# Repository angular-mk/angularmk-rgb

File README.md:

# angularmk-rgb
## Angular RGB Mechanical Keyboard

### Description

The AngularRGB is a, minimalistic, 40% keyboard that supports perkey RGB Lighting. We've noticed that there are no purchasing options for anyone interested in a rgb per key backlit keyboard, so we decided to create one.
[Website Description](https://angularmk.xyz/angular-rgb/)

The PCB consists of a 4x12 matrix layed out as a COL to ROW diode configuration with a staggered design. Additionally, there are slots cut out on the board to provide the space for the WS2812B-Mini RGB LEDs that provide the lighting. There are also numerous protection features, such as ESD protections for both the data lines aswell as the power lines; fueses protecting the precious microcontroller in a case of short circuit; and many more.

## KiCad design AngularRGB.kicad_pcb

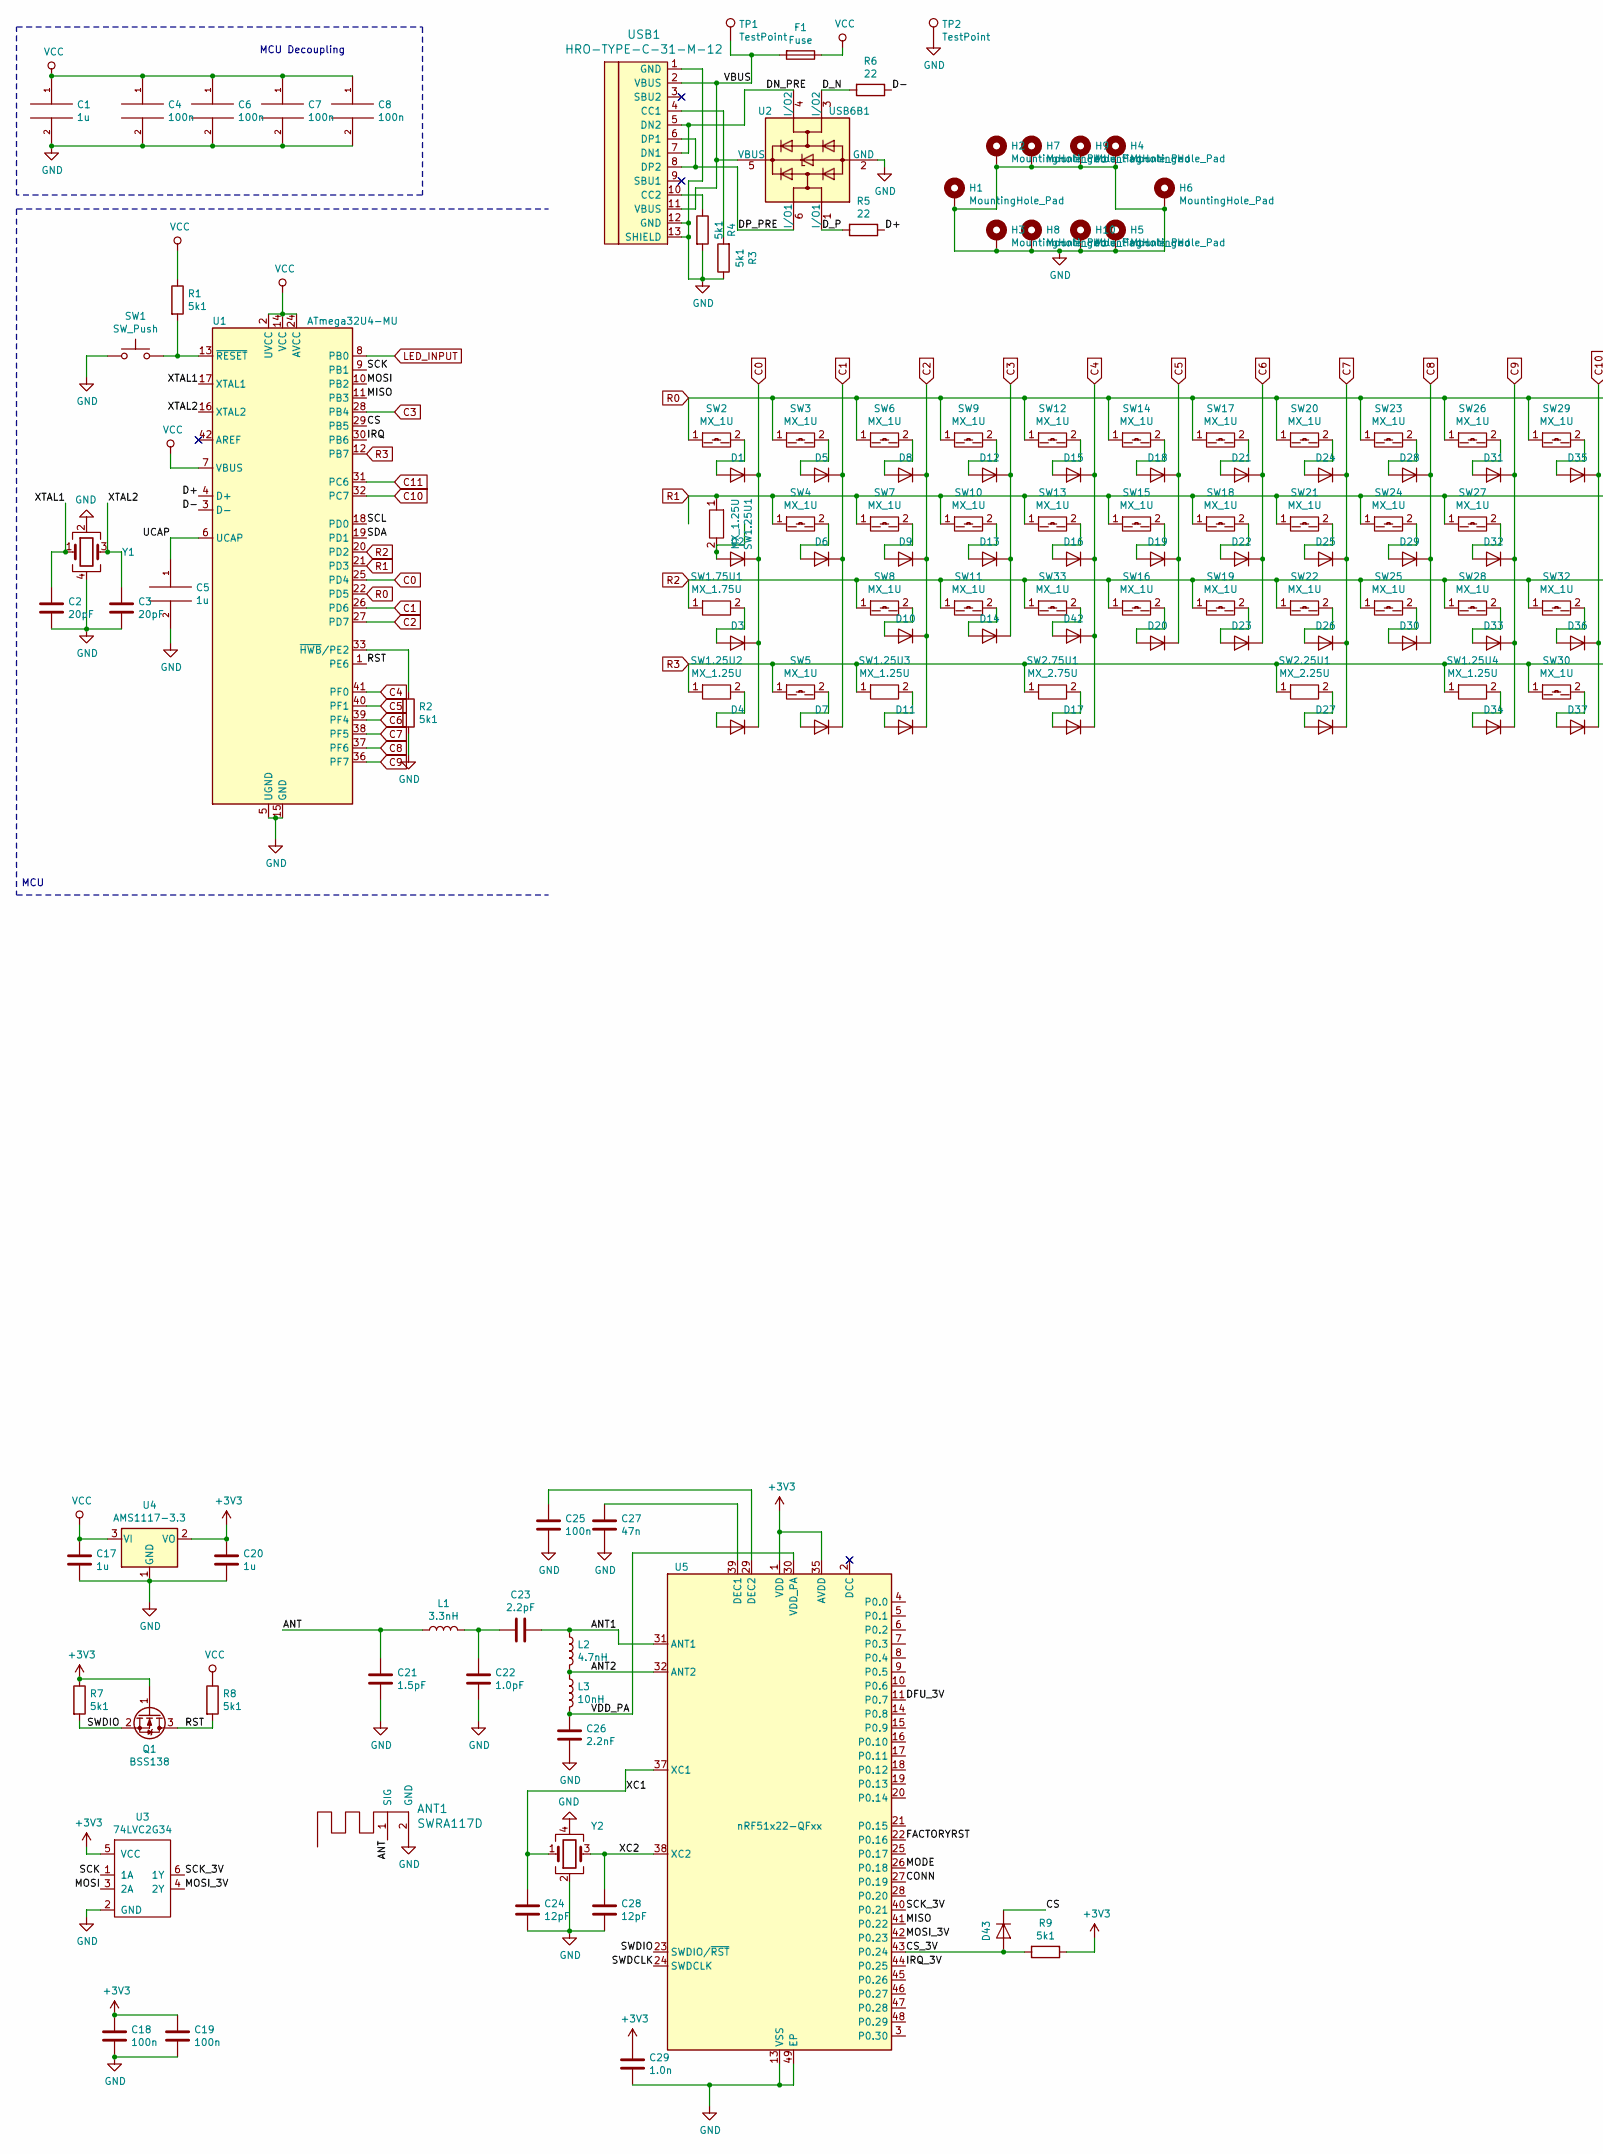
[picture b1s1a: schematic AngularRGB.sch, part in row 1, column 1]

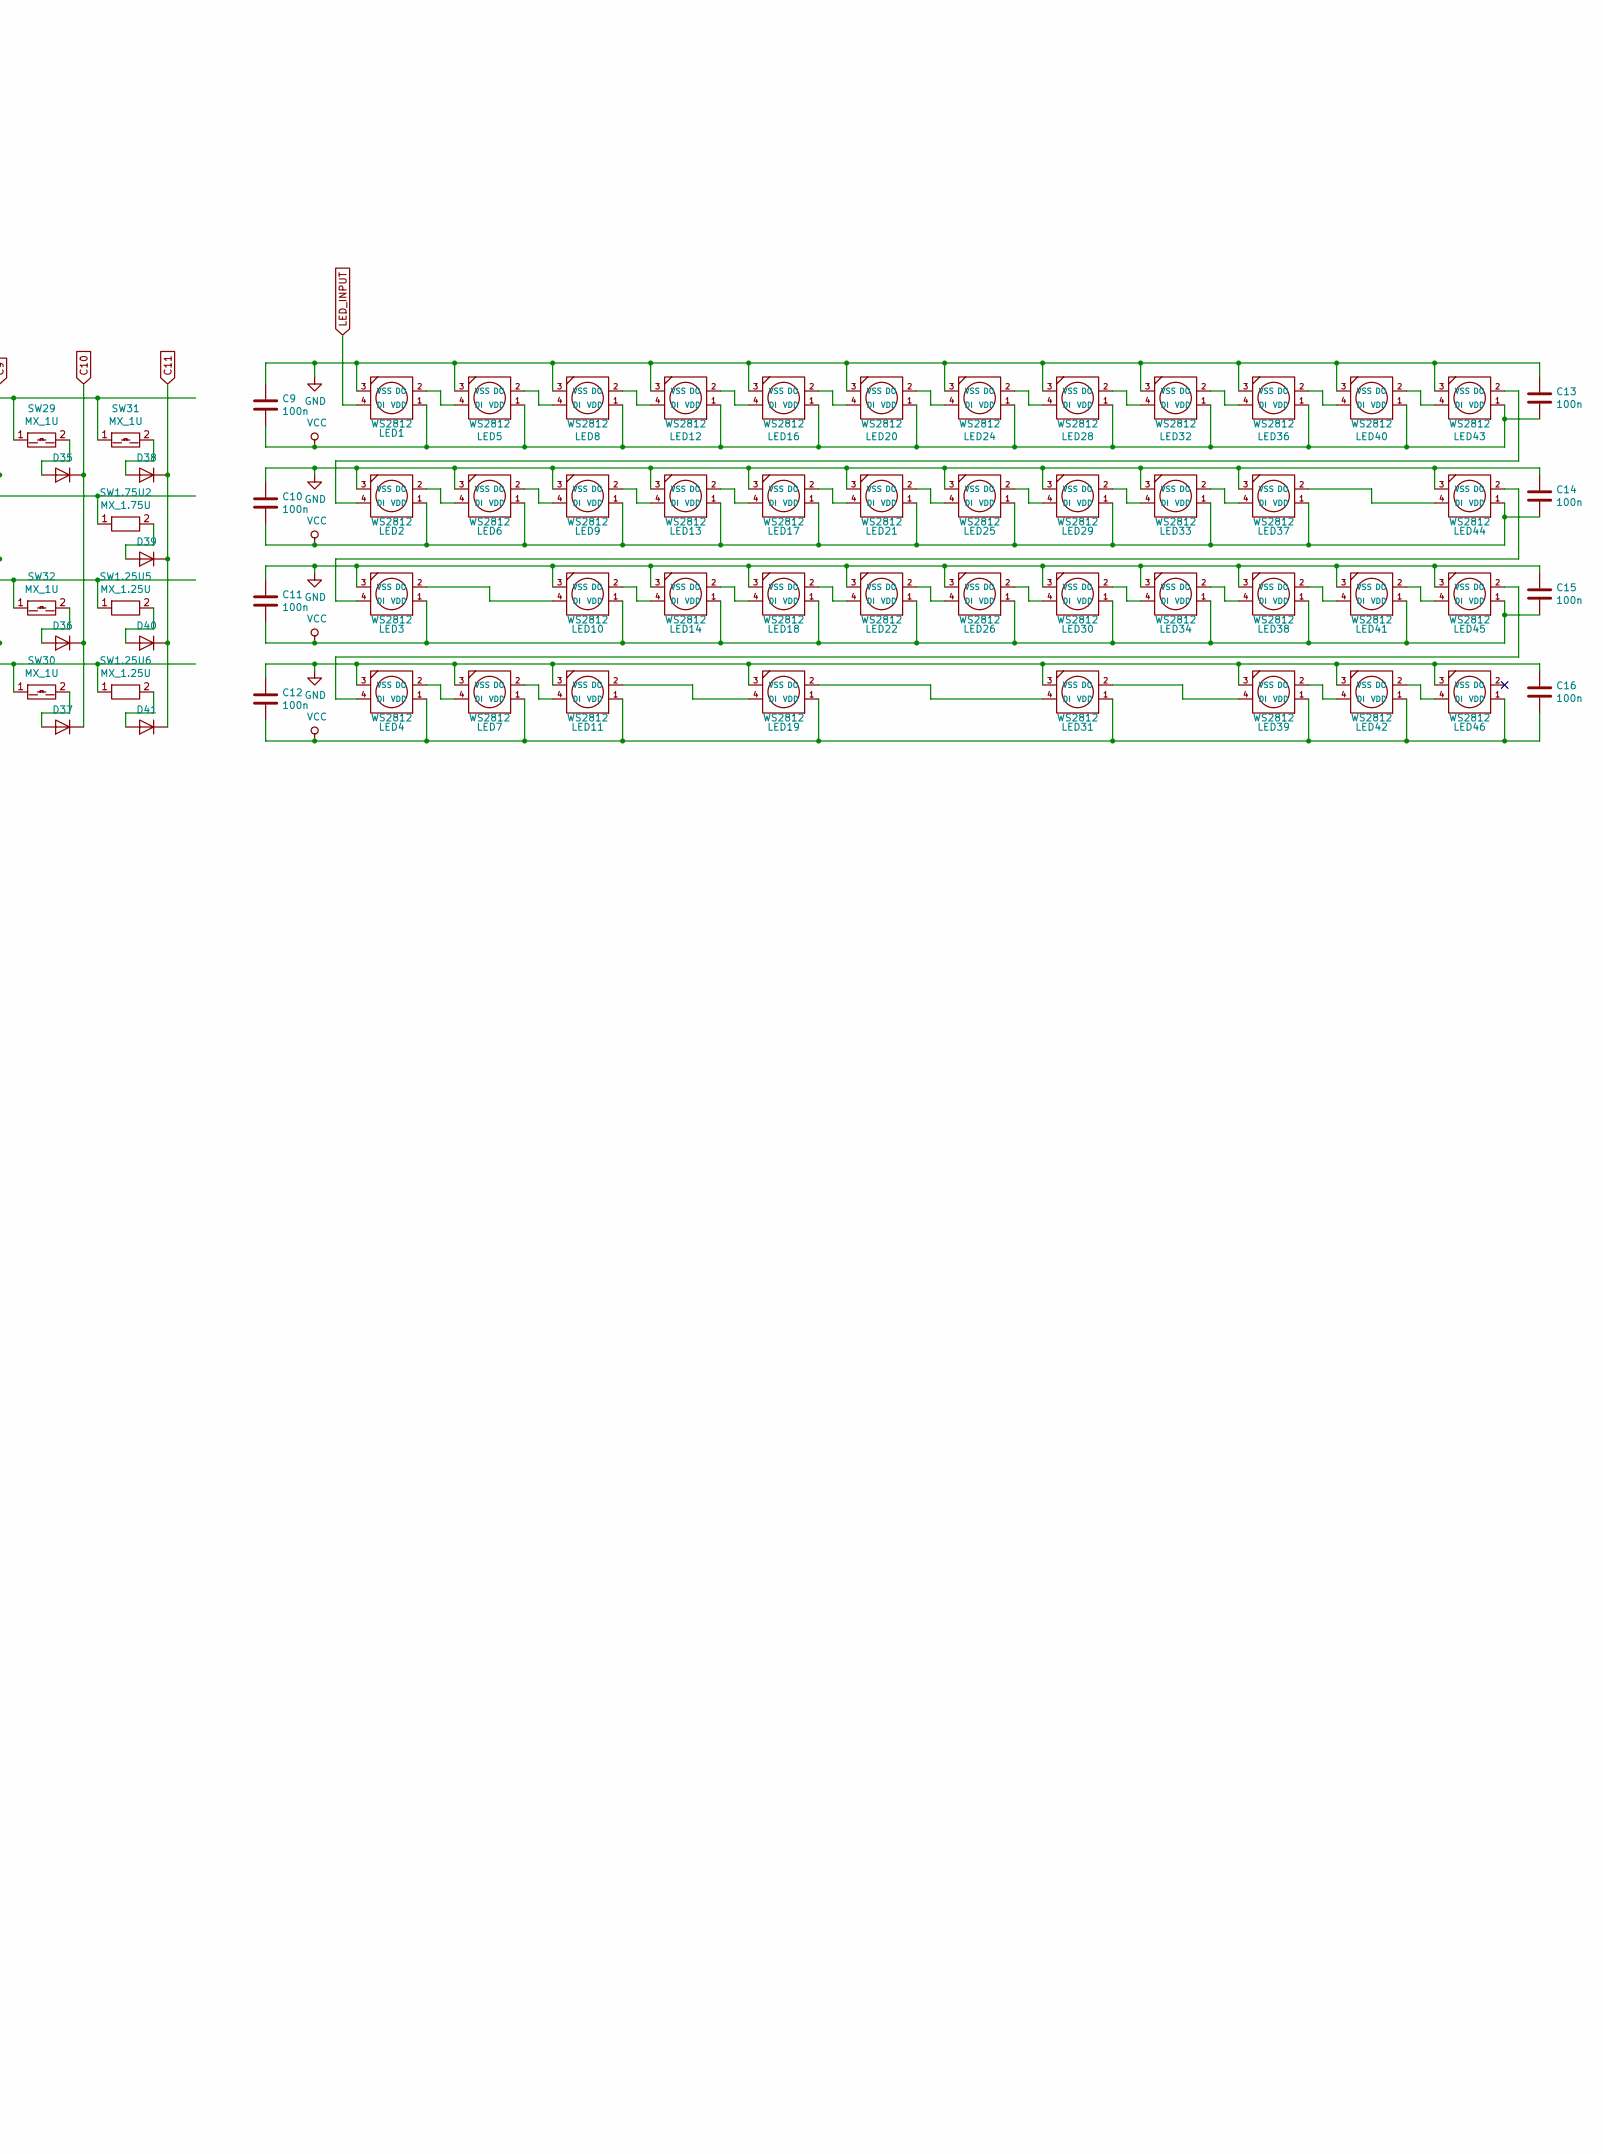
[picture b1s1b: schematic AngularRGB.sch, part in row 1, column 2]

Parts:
ANT1: SWRA117D; Texas_SWRA117D_2.4GHz_Right
C1, C5, C17, C20: 1u; C_0603_1608Metric
C2, C3: 20pF; C_0603_1608Metric
C4, C6, C7, C8, C9, C10, C11, C12, C13, C14, C15, C16, C18, C19, C25: 100n; C_0603_1608Metric
C21: 1.5pF; C_0603_1608Metric
C22: 1.0pF; C_0603_1608Metric
C23: 2.2pF; C_0603_1608Metric
C24, C28: 12pF; C_0603_1608Metric
C26: 2.2nF; C_0603_1608Metric
C27: 47n; C_0603_1608Metric
C29: 1.0n; C_0603_1608Metric
D1: D; D_SOD-123F
D2, D3, D4, D5, D6, D7, D8, D9, D10, D11, D12, D13, D14, D15, D16, D17, D18, D19, D20, D21, D22, D23, D24, D25, D26, D27, D28, D29, D30, D31, D32, D33, D34, D35, D36, D37, D38, D39, D40, D41, D42, D43: D; D_SOD-123
F1: Fuse; Fuse_0603_1608Metric
H1, H2, H3, H4, H5, H6, H7, H8, H9, H10: MountingHole_Pad; MountingHole_2.2mm_M2_DIN965_Pad
L1: 3.3nH; L_0603_1608Metric
L2: 4.7nH; L_0603_1608Metric
L3: 10nH; L_0603_1608Metric
LED1, LED2, LED3, LED4, LED5, LED6, LED7, LED8, LED9, LED10, LED11, LED12, LED13, LED14, LED16, LED17, LED18, LED19, LED20, LED21, LED22, LED24, LED25, LED26, LED28, LED29, LED30, LED31, LED32, LED33, LED34, LED36, LED37, LED38, LED39, LED40, LED41, LED42, LED43, LED44, LED45, LED46: WS2812; REVERSE_LED
Q1: BSS138; SOT-23
R1, R2, R3, R4, R7, R8, R9: 5k1; R_0603_1608Metric
R5, R6: 22; R_0603_1608Metric
SW1: SW_Push; SPST-NO-4
SW1.25U1, SW1.25U2, SW1.25U3, SW1.25U4, SW1.25U5, SW1.25U6: MX_1.25U
SW1.75U1, SW1.75U2: MX_1.75U; MX-1.75U
SW2, SW3, SW4, SW5, SW6, SW7, SW8, SW9, SW10, SW11, SW12, SW13, SW14, SW15, SW16, SW17, SW18, SW19, SW20, SW21, SW22, SW23, SW24, SW25, SW26, SW27, SW28, SW29, SW30, SW31, SW32, SW33: MX_1U; MX-1U
SW2.25U1: MX_2.25U; MX-2.25U
SW2.75U1: MX_2.75U; MX-2.75U
TP1, TP2: TestPoint; TestPoint_Pad_D2.0mm
U1: ATmega32U4-MU; QFN-44-1EP_7x7mm_P0.5mm_EP5.2x5.2mm
U2: USB6B1; SOT-23-6
U3: 74LVC2G34; SOT-23-6
U4: AMS1117-3.3; SOT-223-3_TabPin2
U5: nRF51x22-QFxx; QFN-48-1EP_6x6mm_P0.4mm_EP4.66x4.66mm
USB1: HRO-TYPE-C-31-M-12; HRO-TYPE-C-31-M-12-Assembly
Y1, Y2: Crystal_GND24; Crystal_SMD_3225-4Pin_3.2x2.5mm

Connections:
+3V3: C18.1, C19.1, C20.1, C29.1, Q1.1 (G), R7.1, R9.1, U3.5 (VCC), U4.2 (VO), U5.1 (VDD), U5.12 (VDD), U5.35 (AVDD), U5.36 (AVDD)
/ANT: ANT1.1 (SIG), C21.1, L1.1
/ANT1: C23.1, L2.1, U5.31 (ANT1)
/ANT2: L2.2, L3.1, U5.32 (ANT2)
/CONN: U5.27 (P0.19)
/CS: D43.1 (K), U1.29 (PB5)
/CS_3V: D43.2 (A), R9.2, U5.43 (P0.24)
/D+: R5.1, U1.4 (D+)
/D-: R6.1, U1.3 (D-)
/DFU_3V: U5.11 (P0.7)
/DN_PRE: U2.4 (I/O2), USB1.5 (DN2), USB1.7 (DN1)
/DP_PRE: U2.6 (I/O1), USB1.6 (DP1), USB1.8 (DP2)
/D_N: R6.2, U2.3 (I/O2)
/D_P: R5.2, U2.1 (I/O1)
/FACTORYRST: U5.22 (P0.16)
/IRQ: U1.30 (PB6)
/IRQ_3V: U5.44 (P0.25)
/MISO: U1.11 (PB3), U5.41 (P0.22)
/MODE: U5.26 (P0.18)
/MOSI: U1.10 (PB2), U3.3 (2A)
/MOSI_3V: U3.4 (2Y), U5.42 (P0.23)
/RST: Q1.3 (D), R8.2, U1.1 (PE6)
/SCK: U1.9 (PB1), U3.1 (1A)
/SCK_3V: U3.6 (1Y), U5.40 (P0.21)
/SCL: U1.18 (PD0)
/SDA: U1.19 (PD1)
/SWDCLK: U5.24 (SWDCLK)
/SWDIO: Q1.2 (S), R7.2, U5.23 (SWDIO/~RST)
/UCAP: C5.1, U1.6 (UCAP)
/VBUS: F1.2, TP1.1, U2.5 (VBUS), USB1.2 (VBUS), USB1.11 (VBUS)
/VDD_PA: C26.1, L3.2, U5.30 (VDD_PA)
/XC1: C24.1, U5.37 (XC1), Y2.1
/XC2: C28.1, U5.38 (XC2), Y2.3
/XTAL1: C2.1, U1.17 (XTAL1), Y1.1
/XTAL2: C3.1, U1.16 (XTAL2), Y1.3
C0: D1.1 (K), D2.1 (K), D3.1 (K), D4.1 (K), U1.25 (PD4)
C1: D5.1 (K), D6.1 (K), D7.1 (K), U1.26 (PD6)
C2: D8.1 (K), D9.1 (K), D10.1 (K), D11.1 (K), U1.27 (PD7)
C3: D12.1 (K), D13.1 (K), D14.1 (K), U1.28 (PB4)
C4: D15.1 (K), D16.1 (K), D17.1 (K), D42.1 (K), U1.41 (PF0)
C5: D18.1 (K), D19.1 (K), D20.1 (K), U1.40 (PF1)
C6: D21.1 (K), D22.1 (K), D23.1 (K), U1.39 (PF4)
C7: D24.1 (K), D25.1 (K), D26.1 (K), D27.1 (K), U1.38 (PF5)
C8: D28.1 (K), D29.1 (K), D30.1 (K), U1.37 (PF6)
C9: D31.1 (K), D32.1 (K), D33.1 (K), D34.1 (K), U1.36 (PF7)
C10: D35.1 (K), D36.1 (K), D37.1 (K), U1.32 (PC7)
C11: D38.1 (K), D39.1 (K), D40.1 (K), D41.1 (K), U1.31 (PC6)
GND: ANT1.2 (GND), C1.2, C2.2, C3.2, C4.2, C5.2, C6.2, C7.2, C8.2, C9.2, C10.2, C11.2, C12.2, C13.1, C14.1, C15.1, C16.1, C17.2, C18.2, C19.2, C20.2, C21.2, C22.2, C24.2, C25.2, C26.2, C27.2, C28.2, C29.2, H1.1, H2.1, H3.1, H4.1, H5.1, H6.1, H7.1, H8.1, H9.1, H10.1, LED1.3 (VSS), LED2.3 (VSS), LED3.3 (VSS), LED4.3 (VSS), LED5.3 (VSS), LED6.3 (VSS), LED7.3 (VSS), LED8.3 (VSS), LED9.3 (VSS), LED10.3 (VSS), LED11.3 (VSS), LED12.3 (VSS), LED13.3 (VSS), LED14.3 (VSS), LED16.3 (VSS), LED17.3 (VSS), LED18.3 (VSS), LED19.3 (VSS), LED20.3 (VSS), LED21.3 (VSS), LED22.3 (VSS), LED24.3 (VSS), LED25.3 (VSS), LED26.3 (VSS), LED28.3 (VSS), LED29.3 (VSS), LED30.3 (VSS), LED31.3 (VSS), LED32.3 (VSS), LED33.3 (VSS), LED34.3 (VSS), LED36.3 (VSS), LED37.3 (VSS), LED38.3 (VSS), LED39.3 (VSS), LED40.3 (VSS), LED41.3 (VSS), LED42.3 (VSS), LED43.3 (VSS), LED44.3 (VSS), LED45.3 (VSS), LED46.3 (VSS), R2.2, R3.1, R4.2, SW1.1, TP2.1, U1.5 (UGND), U1.15 (GND), U1.23 (GND), U1.35 (GND), U1.43 (GND), U1.45 (GND), U2.2 (GND), U3.2 (GND), U4.1 (GND), U5.13 (VSS), U5.33 (VSS), U5.34 (VSS), U5.49 (EP), USB1.1 (GND), USB1.12 (GND), USB1.13 (SHIELD), Y1.2, Y1.4, Y2.2, Y2.4
LED_INPUT: LED1.4 (DI), U1.8 (PB0)
unnamed: C22.1, C23.2, L1.2
unnamed: C25.1, U5.29 (DEC2)
unnamed: C27.1, U5.39 (DEC1)
unnamed: D1.2 (A), SW2.2
unnamed: D2.2 (A), SW1.25U1.2
unnamed: D3.2 (A), SW1.75U1.2
unnamed: D4.2 (A), SW1.25U2.2
unnamed: D5.2 (A), SW3.2
unnamed: D6.2 (A), SW4.2
unnamed: D7.2 (A), SW5.2
unnamed: D8.2 (A), SW6.2
unnamed: D9.2 (A), SW7.2
unnamed: D10.2 (A), SW8.2
unnamed: D11.2 (A), SW1.25U3.2
unnamed: D12.2 (A), SW9.2
unnamed: D13.2 (A), SW10.2
unnamed: D14.2 (A), SW11.2
unnamed: D15.2 (A), SW12.2
unnamed: D16.2 (A), SW13.2
unnamed: D17.2 (A), SW2.75U1.2
unnamed: D18.2 (A), SW14.2
unnamed: D19.2 (A), SW15.2
unnamed: D20.2 (A), SW16.2
unnamed: D21.2 (A), SW17.2
unnamed: D22.2 (A), SW18.2
unnamed: D23.2 (A), SW19.2
unnamed: D24.2 (A), SW20.2
unnamed: D25.2 (A), SW21.2
unnamed: D26.2 (A), SW22.2
unnamed: D27.2 (A), SW2.25U1.2
unnamed: D28.2 (A), SW23.2
unnamed: D29.2 (A), SW24.2
unnamed: D30.2 (A), SW25.2
unnamed: D31.2 (A), SW26.2
unnamed: D32.2 (A), SW27.2
unnamed: D33.2 (A), SW28.2
unnamed: D34.2 (A), SW1.25U4.2
unnamed: D35.2 (A), SW29.2
unnamed: D36.2 (A), SW32.2
unnamed: D37.2 (A), SW30.2
unnamed: D38.2 (A), SW31.2
unnamed: D39.2 (A), SW1.75U2.2
unnamed: D40.2 (A), SW1.25U5.2
unnamed: D41.2 (A), SW1.25U6.2
unnamed: D42.2 (A), SW33.2
unnamed: LED1.2 (DO), LED5.4 (DI)
unnamed: LED2.2 (DO), LED6.4 (DI)
unnamed: LED2.4 (DI), LED43.2 (DO)
unnamed: LED3.4 (DI), LED44.2 (DO)
unnamed: LED4.2 (DO), LED7.4 (DI)
unnamed: LED4.4 (DI), LED45.2 (DO)
unnamed: LED5.2 (DO), LED8.4 (DI)
unnamed: LED6.2 (DO), LED9.4 (DI)
unnamed: LED10.2 (DO), LED14.4 (DI)
unnamed: LED3.2 (DO), LED10.4 (DI)
unnamed: LED11.2 (DO), LED19.4 (DI)
unnamed: LED7.2 (DO), LED11.4 (DI)
unnamed: LED12.2 (DO), LED16.4 (DI)
unnamed: LED8.2 (DO), LED12.4 (DI)
unnamed: LED13.2 (DO), LED17.4 (DI)
unnamed: LED9.2 (DO), LED13.4 (DI)
unnamed: LED14.2 (DO), LED18.4 (DI)
unnamed: LED16.2 (DO), LED20.4 (DI)
unnamed: LED17.2 (DO), LED21.4 (DI)
unnamed: LED18.2 (DO), LED22.4 (DI)
unnamed: LED19.2 (DO), LED31.4 (DI)
unnamed: LED20.2 (DO), LED24.4 (DI)
unnamed: LED21.2 (DO), LED25.4 (DI)
unnamed: LED22.2 (DO), LED26.4 (DI)
unnamed: LED24.2 (DO), LED28.4 (DI)
unnamed: LED25.2 (DO), LED29.4 (DI)
unnamed: LED26.2 (DO), LED30.4 (DI)
unnamed: LED28.2 (DO), LED32.4 (DI)
unnamed: LED29.2 (DO), LED33.4 (DI)
unnamed: LED30.2 (DO), LED34.4 (DI)
unnamed: LED31.2 (DO), LED39.4 (DI)
unnamed: LED32.2 (DO), LED36.4 (DI)
unnamed: LED33.2 (DO), LED37.4 (DI)
unnamed: LED34.2 (DO), LED38.4 (DI)
unnamed: LED36.2 (DO), LED40.4 (DI)
unnamed: LED37.2 (DO), LED44.4 (DI)
unnamed: LED38.2 (DO), LED41.4 (DI)
unnamed: LED39.2 (DO), LED42.4 (DI)
unnamed: LED40.2 (DO), LED43.4 (DI)
unnamed: LED41.2 (DO), LED45.4 (DI)
unnamed: LED42.2 (DO), LED46.4 (DI)
unnamed: R1.2, SW1.2, U1.13 (~RESET)
unnamed: R2.1, U1.33 (~HWB~/PE2)
unnamed: R3.2, USB1.4 (CC1)
unnamed: R4.1, USB1.10 (CC2)
R0: SW2.1, SW3.1, SW6.1, SW9.1, SW12.1, SW14.1, SW17.1, SW20.1, SW23.1, SW26.1, SW29.1, SW31.1, U1.22 (PD5)
R1: SW1.25U1.1, SW1.75U2.1, SW4.1, SW7.1, SW10.1, SW13.1, SW15.1, SW18.1, SW21.1, SW24.1, SW27.1, U1.21 (PD3)
R2: SW1.25U5.1, SW1.75U1.1, SW8.1, SW11.1, SW16.1, SW19.1, SW22.1, SW25.1, SW28.1, SW32.1, SW33.1, U1.20 (PD2)
R3: SW1.25U2.1, SW1.25U3.1, SW1.25U4.1, SW1.25U6.1, SW2.25U1.1, SW2.75U1.1, SW5.1, SW30.1, U1.12 (PB7)
VCC: C1.1, C4.1, C6.1, C7.1, C8.1, C9.1, C10.1, C11.1, C12.1, C13.2, C14.2, C15.2, C16.2, C17.1, F1.1, LED1.1 (VDD), LED2.1 (VDD), LED3.1 (VDD), LED4.1 (VDD), LED5.1 (VDD), LED6.1 (VDD), LED7.1 (VDD), LED8.1 (VDD), LED9.1 (VDD), LED10.1 (VDD), LED11.1 (VDD), LED12.1 (VDD), LED13.1 (VDD), LED14.1 (VDD), LED16.1 (VDD), LED17.1 (VDD), LED18.1 (VDD), LED19.1 (VDD), LED20.1 (VDD), LED21.1 (VDD), LED22.1 (VDD), LED24.1 (VDD), LED25.1 (VDD), LED26.1 (VDD), LED28.1 (VDD), LED29.1 (VDD), LED30.1 (VDD), LED31.1 (VDD), LED32.1 (VDD), LED33.1 (VDD), LED34.1 (VDD), LED36.1 (VDD), LED37.1 (VDD), LED38.1 (VDD), LED39.1 (VDD), LED40.1 (VDD), LED41.1 (VDD), LED42.1 (VDD), LED43.1 (VDD), LED44.1 (VDD), LED45.1 (VDD), LED46.1 (VDD), R1.1, R8.1, U1.2 (UVCC), U1.7 (VBUS), U1.14 (VCC), U1.24 (AVCC), U1.34 (VCC), U1.44 (AVCC), U4.3 (VI)

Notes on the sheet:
MCU Decoupling
MCU

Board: 4 copper layers, 192 parts (94 on the bottom side), 135 nets, no tracks yet.

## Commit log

2019-04-16 MCU Connections
2019-04-16 USB Sch
2019-04-17 USB Port
2019-04-17 Matrix Layout
2019-04-17 Annotation
2019-04-17 Addded PCB Footprints
2019-04-17 Footprint Linking
2019-04-18 Layout
2019-04-18 WS2812B-Mini Symbole
2019-04-18 Reverse mount WS2812B LED Footprint
2019-04-18 Led matrix
2019-04-18 LED Matrix Sch
2019-04-18 LED Matrix Placement
2019-04-18 LED Matrix Footprint swap
2019-04-18 Matrix Connections
2019-04-19 Finsihed Layout
2019-04-19 Copper Pour
2019-04-19 Fixed LED Input
2019-04-20 Top Plate Init
2019-04-21 Added Case Design
2019-04-22 Added the case
2019-04-22 Temp
2019-04-23 Cleaning up
2019-04-23 Exported CAD Files
2019-04-25 Added QMK Firmware
2019-04-26 Changed Keymaps
